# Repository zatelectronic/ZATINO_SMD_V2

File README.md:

<div align="center">

# ZATINO V2 SMD

**Placa de desenvolvimento compatível com Arduino Uno, totalmente SMD, com programação USB-C integrada via módulo FT232RL**

</div>

---

## 📋 Índice

- [ZATINO V2 SMD](#zatino-v2-smd)
  - [📋 Índice](#-índice)
  - [Visão Geral](#visão-geral)
  - [Renders 3D](#renders-3d)
  - [Funcionalidades](#funcionalidades)
  - [Especificações Técnicas](#especificações-técnicas)
  - [Lista de Materiais](#lista-de-materiais)
  - [Arquitetura de Alimentação](#arquitetura-de-alimentação)
  - [Compatibilidade de Pinos](#compatibilidade-de-pinos)
  - [Estrutura do Repositório](#estrutura-do-repositório)
  - [Como Usar](#como-usar)
    - [Abrindo no KiCad](#abrindo-no-kicad)
    - [Programando a Placa](#programando-a-placa)
  - [Sobre](#sobre)

---

## Visão Geral

**ZATINO V2 SMD** é uma placa de desenvolvimento personalizada, compatível com Arduino Uno, projetada do zero pela **ZAT ELECTRONIC** utilizando o **KICAD 10**. A placa substitui todos os componentes através-furo por componentes SMD, resultando em uma PCB mais limpa, compacta e com aparência profissional.

O projeto utiliza o **ATmega328PB-AU** (TQFP-32) como microcontrolador principal, com um módulo **FT232RL USB-C** encaixado em um conector fêmea de 6 pinos para programação serial e comunicação USB — mantendo o conector USB-C montado verticalmente na borda da placa para um acabamento elegante.

> 💡 Esta placa mantém **total compatibilidade de pinos com o Arduino Uno R3**, permitindo o uso de shields e bibliotecas existentes sem qualquer modificação.

---

## Renders 3D

<div align="center">

*Vista superior — posicionamento dos componentes e serigrafias*

<br/>

*Vista isométrica — módulo FT232RL USB-C e montagem geral da placa*

</div>

---

## Funcionalidades

- ✅ **ATmega328PB-AU** — encapsulamento SMD TQFP-32, 100% compatível com Arduino Uno
- ✅ **Programação via USB-C** pelo módulo FT232RL (conector plugável)
- ✅ **Duplo regulador de tensão** — 5V (AMS1117-5.0) e 3,3V (AMS1117-3.3)
- ✅ **Proteção contra inversão de polaridade** via diodo 1N4007 na entrada de alimentação
- ✅ **Oscilador a cristal de 16 MHz** (encapsulamento SMD HC-49/SD)
- ✅ **Pinout completo Arduino Uno R3** — conectores Digital, Analógico, Alimentação e ICSP
- ✅ **LEDs de status** (footprint SMD 1210)
- ✅ **Botão de reset tátil** (SMD 6×6×5 mm)
- ✅ **Entrada de alimentação Barrel Jack (P4)** com chave integrada
- ✅ **Projetado com KICAD 10** — EDA totalmente open source
- ✅ **Logotipo Open Source Hardware** certificado na PCB

---

## Especificações Técnicas

| Parâmetro | Valor |
|-----------|-------|
| **Microcontrolador** | ATmega328PB-AU (TQFP-32) |
| **Velocidade de Clock** | 16 MHz (cristal externo) |
| **Tensão de Operação** | 5V |
| **Tensão de Entrada** | 7–12V (Barrel Jack P4) |
| **Saída 3,3V** | AMS1117-3.3 (até 800mA) |
| **Regulador 5V** | AMS1117-5.0 |
| **Interface USB** | USB-C via módulo FT232RL |
| **Pinos Digital I/O** | 14 (D0–D13), PWM em D3, D5, D6, D9, D10, D11 |
| **Entradas Analógicas** | 6 (A0–A5) |
| **Memória Flash** | 32 KB (ATmega328PB) |
| **SRAM** | 2 KB |
| **EEPROM** | 1 KB |
| **Ferramenta de Projeto** | KICAD 10.0 |
| **Versão da PCB** | V2 — 2026 |
| **Fator de Forma** | Compatível com Arduino Uno R3 |

---

## Lista de Materiais

| Ref | Componente | Valor / Parte | Encapsulamento |
|-----|-----------|--------------|----------------|
| U2 | Microcontrolador | ATmega328PB-AU | TQFP-32 |
| REGULADOR_5V1 | Regulador de Tensão 5V | AMS1117-5.0 | SOT-223 |
| REGULADOR_3V3 | Regulador de Tensão 3,3V | AMS1117-3.3 | SOT-223 |
| KR1 | Oscilador a Cristal | 16 MHz | HC-49/SD SMD |
| BARRA_DE_PINO2 | Conector FTDI | FT232RL USB-C | Fêmea 6 pinos 2,54mm |
| A2 | Referência de Pinout | Arduino Uno R3 | — |
| D1 | Diodo Retificador | 1N4007 | SMA |
| L1, L2 | LEDs de Status | LED 5MM | 1210 (3225) SMD |
| R1 | Resistor de LED | 470Ω | 1206 |
| R2 | Resistor de LED | 220Ω | 1206 |
| R3 | Resistor de Pull-up | 10KΩ | 1206 |
| C1, C2, C3 | Capacitores Eletrolíticos | 10µF | CP Elec 4×5.4 |
| C4, C5 | Capacitores de Cristal | 22pF | 0805 |
| C6, C7 | Capacitores de Bypass | 100nF | 0805 |
| CONECTOR1 | Conector de Alimentação DC | Barrel Jack P4 | Horizontal |
| BARRA_DE_PINO1 | Conector Auxiliar | 2 terminais | 2,54mm |
| TACTIL_SWITCH1 | Botão de Reset | 6×6×5mm | SMD Tátil |
| TP1 | Ponto de Teste | — | SMD |

---

## Arquitetura de Alimentação

```
VIN (Barrel Jack P4)
        │
    [1N4007]  ← Proteção contra inversão de polaridade
        │
   ┌────┴────┐
   │         │
[AMS1117-5.0]  [AMS1117-3.3]
   │         │
  +5V       +3,3V
   │
[ATmega328PB-AU]
   │
[FT232RL USB-C] ← UART TX/RX + DTR (auto-reset)
```

A placa suporta duas fontes de alimentação:
- **Barrel Jack (P4)** — entrada de 7 a 12V DC, regulada para 5V e 3,3V internamente
- **USB-C via módulo FT232RL** — 5V direto do USB, alimentando o rail VCC quando conectado

---

## Compatibilidade de Pinos

A placa expõe o **pinout completo do Arduino Uno R3**:

| Conector | Pinos |
|----------|-------|
| Digital (PWM) | D0–D13, com PWM em ~3, ~5, ~6, ~9, ~10, ~11 |
| Entradas Analógicas | A0–A5 |
| Alimentação | VIN, 5V, 3V3, GND, AREF, IOREF, RESET |
| ICSP | MISO, MOSI, SCK, RESET, VCC, GND |
| UART (FT232RL) | TX, RX (via conector BARRA_DE_PINO2) |
| I2C | SDA (A4), SCL (A5) |

---

## Estrutura do Repositório

```
ZATINO_SMD_V2/
├── ZATINO_SMD_V2.kicad_pro       # Arquivo de projeto KiCad
├── ZATINO_SMD_V2.kicad_sch       # Esquemático (KICAD 10)
├── ZATINO_SMD_V2.kicad_pcb       # Layout da PCB (KICAD 10)
├── ZATINO_SMD_V2.kicad_prl       # Configurações locais do projeto
├── packages3D/                   # Modelos 3D arquivados (STEP / WRL)
│   ├── ATmega_AP214.STEP
│   ├── AMS1117_3V3_axisY.step
│   ├── AMS1117_5V_axisY.step
│   ├── Waveshare_FT232RL_USB-C.step
│   ├── Tactal Switch - SMD 6x6x5.stp
│   └── ...
├── fp-info-cache                 # Cache de footprints
├── fabrication-toolkit-options.json
├── imagem_1.png                  # Render superior da PCB
├── imagem_2.png                  # Render isométrico da PCB
└── README.md
```

---

## Como Usar

### Abrindo no KiCad

1. Instale o **KICAD 10.0** ou superior
2. Clone este repositório:
   ```bash
   git clone https://github.com/seu-usuario/ZATINO_SMD_V2.git
   ```
3. Abra o arquivo `ZATINO_SMD_V2.kicad_pro` no KiCad

### Programando a Placa

1. Encaixe o **módulo FT232RL USB-C** no conector de 6 pinos (`BARRA_DE_PINO2`)
2. Conecte via USB-C ao computador
3. Abra o **Arduino IDE** ou **PlatformIO**
4. Selecione a placa: **Arduino Uno**
5. Selecione a porta COM correta e faça o upload do sketch

## Sobre

<div align="center">

Projetado por **ZAT ELECTRONIC**

*ZATINO V2 SMD — 2026*

</div>

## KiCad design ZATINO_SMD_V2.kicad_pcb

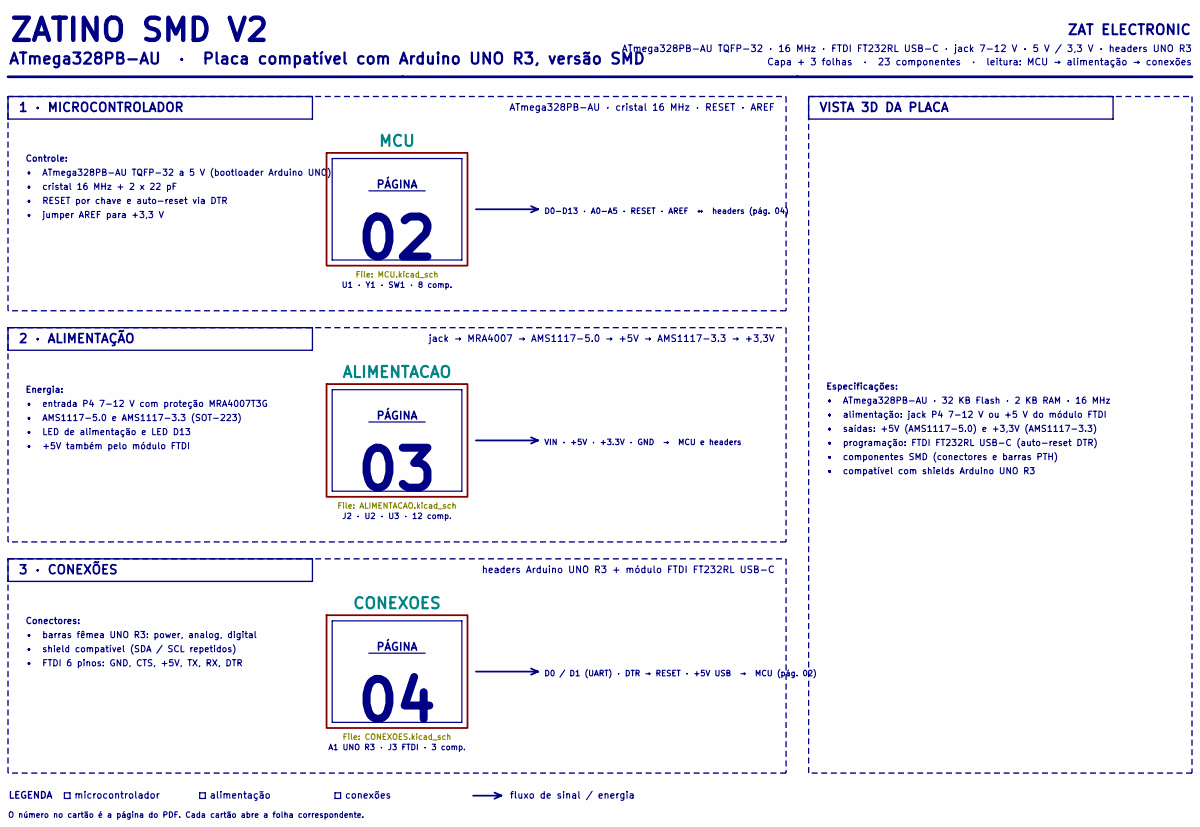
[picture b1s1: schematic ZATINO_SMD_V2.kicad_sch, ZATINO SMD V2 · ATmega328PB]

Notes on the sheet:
PÁGINA
VIN · +5V · +3.3V · GND → MCU e headers
conexões
• compatível com shields Arduino UNO R3
3 · CONEXÕES
• +5V também pelo módulo FTDI
U1 · Y1 · SW1 · 8 comp.
• componentes SMD (conectores e barras PTH)
• LED de alimentação e LED D13
Energia:
VISTA 3D DA PLACA
• ATmega328PB-AU TQFP-32 a 5 V (bootloader Arduino UNO)
• alimentação: jack P4 7-12 V ou +5 V do módulo FTDI
Capa + 3 folhas · 23 componentes · leitura: MCU → alimentação → conexões
D0-D13 · A0-A5 · RESET · AREF ↔ headers (pág. 04)
Especificações:
• RESET por chave e auto-reset via DTR
2 · ALIMENTAÇÃO
• shield compatível (SDA / SCL repetidos)
ZATINO SMD V2
O número no cartão é a página do PDF. Cada cartão abre a folha correspondente.
ATmega328PB-AU · cristal 16 MHz · RESET · AREF
ATmega328PB-AU · Placa compatível com Arduino UNO R3, versão SMD
• FTDI 6 pinos: GND, CTS, +5V, TX, RX, DTR
microcontrolador
• saídas: +5V (AMS1117-5.0) e +3,3V (AMS1117-3.3)
jack → MRA4007 → AMS1117-5.0 → +5V → AMS1117-3.3 → +3,3V
• barras fêmea UNO R3: power, analog, digital
ATmega328PB-AU TQFP-32 · 16 MHz · FTDI FT232RL USB-C · jack 7-12 V · 5 V / 3,3 V · headers UNO R3
A1 UNO R3 · J3 FTDI · 3 comp.
Conectores:
fluxo de sinal / energia
• cristal 16 MHz + 2 x 22 pF
J2 · U2 · U3 · 12 comp.
D0 / D1 (UART) · DTR → RESET · +5V USB → MCU (pág. 02)
• programação: FTDI FT232RL USB-C (auto-reset DTR)
LEGENDA
• ATmega328PB-AU · 32 KB Flash · 2 KB RAM · 16 MHz
• AMS1117-5.0 e AMS1117-3.3 (SOT-223)
• entrada P4 7-12 V com proteção MRA4007T3G

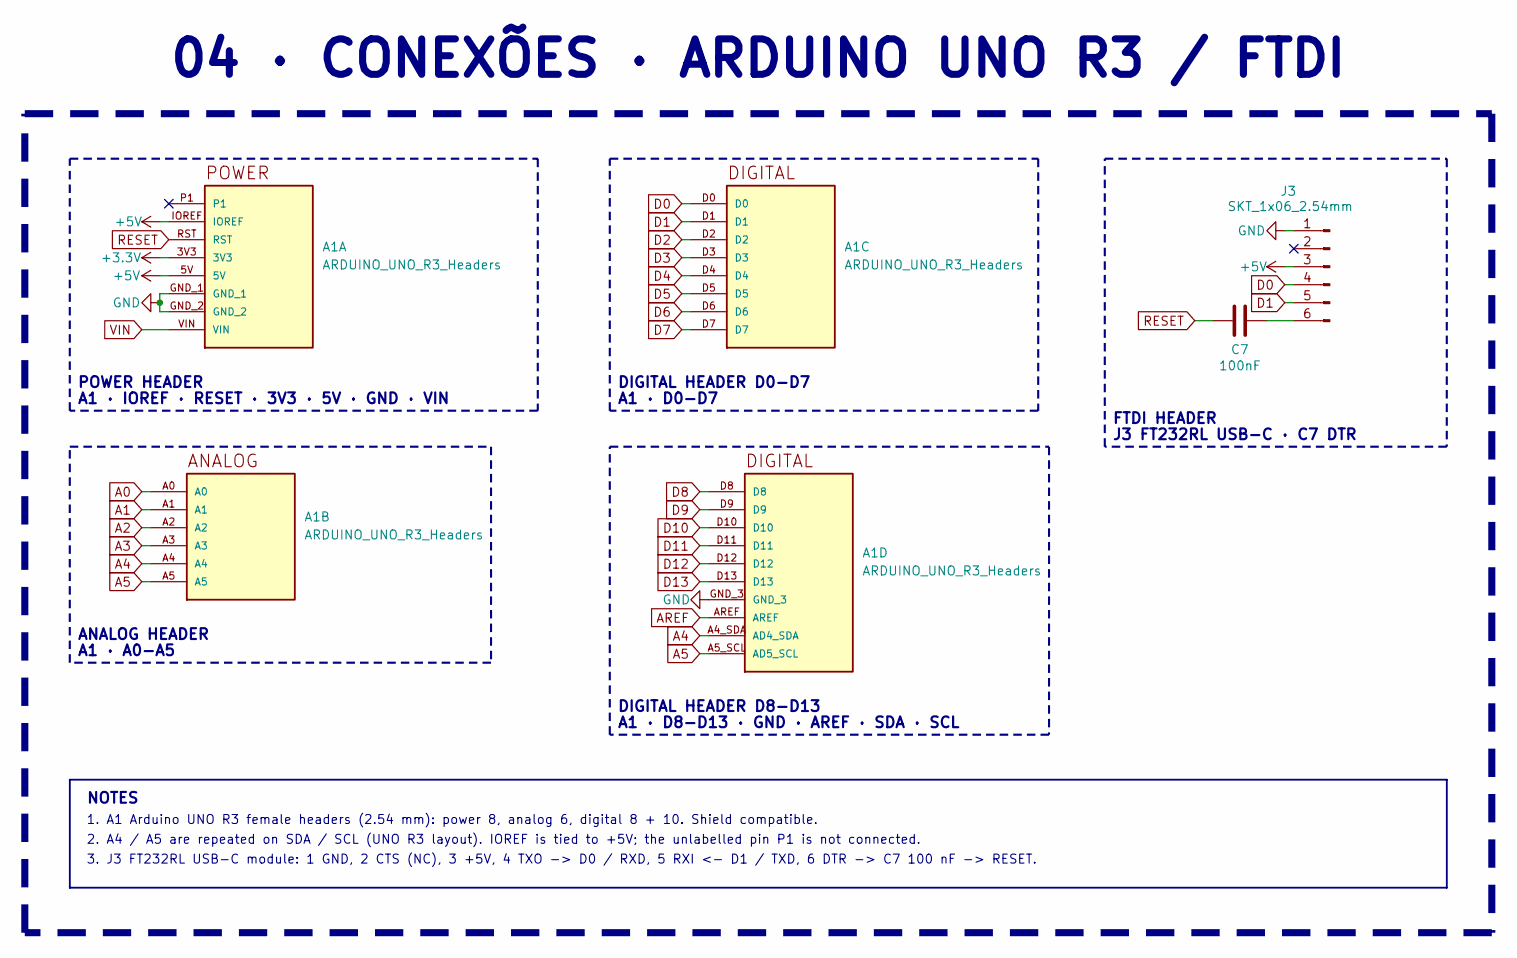
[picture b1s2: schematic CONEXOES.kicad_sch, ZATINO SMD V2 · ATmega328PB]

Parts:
A1: ARDUINO_UNO_R3_Headers
C7: 100nF; C_0805_2012Metric
J3: SKT_1x06_2.54mm; PinSocket_1x06_P2.54mm_Vertical_FT232RL_USB-C

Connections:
+3.3V: A1.3V3; also elsewhere on the board
+5V: A1.5V, A1.IOREF, J3.3; also elsewhere on the board
A0: A1.A0; also elsewhere on the board
A1: A1.A1; also elsewhere on the board
A2: A1.A2; also elsewhere on the board
A3: A1.A3; also elsewhere on the board
A4: A1.A4, A1.A4_SDA (AD4_SDA); also elsewhere on the board
A5: A1.A5, A1.A5_SCL (AD5_SCL); also elsewhere on the board
AREF: A1.AREF; also elsewhere on the board
D0: A1.D0, J3.4; also elsewhere on the board
D1: A1.D1, J3.5; also elsewhere on the board
D2: A1.D2; also elsewhere on the board
D3: A1.D3; also elsewhere on the board
D4: A1.D4; also elsewhere on the board
D5: A1.D5; also elsewhere on the board
D6: A1.D6; also elsewhere on the board
D7: A1.D7; also elsewhere on the board
D8: A1.D8; also elsewhere on the board
D9: A1.D9; also elsewhere on the board
D10: A1.D10; also elsewhere on the board
D11: A1.D11; also elsewhere on the board
D12: A1.D12; also elsewhere on the board
D13: A1.D13; also elsewhere on the board
GND: A1.GND_1, A1.GND_2, A1.GND_3, J3.1; also elsewhere on the board
unnamed: C7.1, J3.6
RESET: A1.RST, C7.2; also elsewhere on the board
VIN: A1.VIN; also elsewhere on the board

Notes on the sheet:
FTDI HEADER
DIGITAL HEADER D0-D7
A1 · D0-D7
1. A1 Arduino UNO R3 female headers (2.54 mm): power 8, analog 6, digital 8 + 10. Shield compatible.
J3 FT232RL USB-C · C7 DTR
ANALOG HEADER
04 · CONEXÕES · ARDUINO UNO R3 / FTDI
2. A4 / A5 are repeated on SDA / SCL (UNO R3 layout). IOREF is tied to +5V; the unlabelled pin P1 is not connected.
DIGITAL HEADER D8-D13
A1 · D8-D13 · GND · AREF · SDA · SCL
3. J3 FT232RL USB-C module: 1 GND, 2 CTS (NC), 3 +5V, 4 TXO -> D0 / RXD, 5 RXI <- D1 / TXD, 6 DTR -> C7 100 nF -> RESET.
A1 · A0-A5
POWER HEADER
A1 · IOREF · RESET · 3V3 · 5V · GND · VIN
NOTES

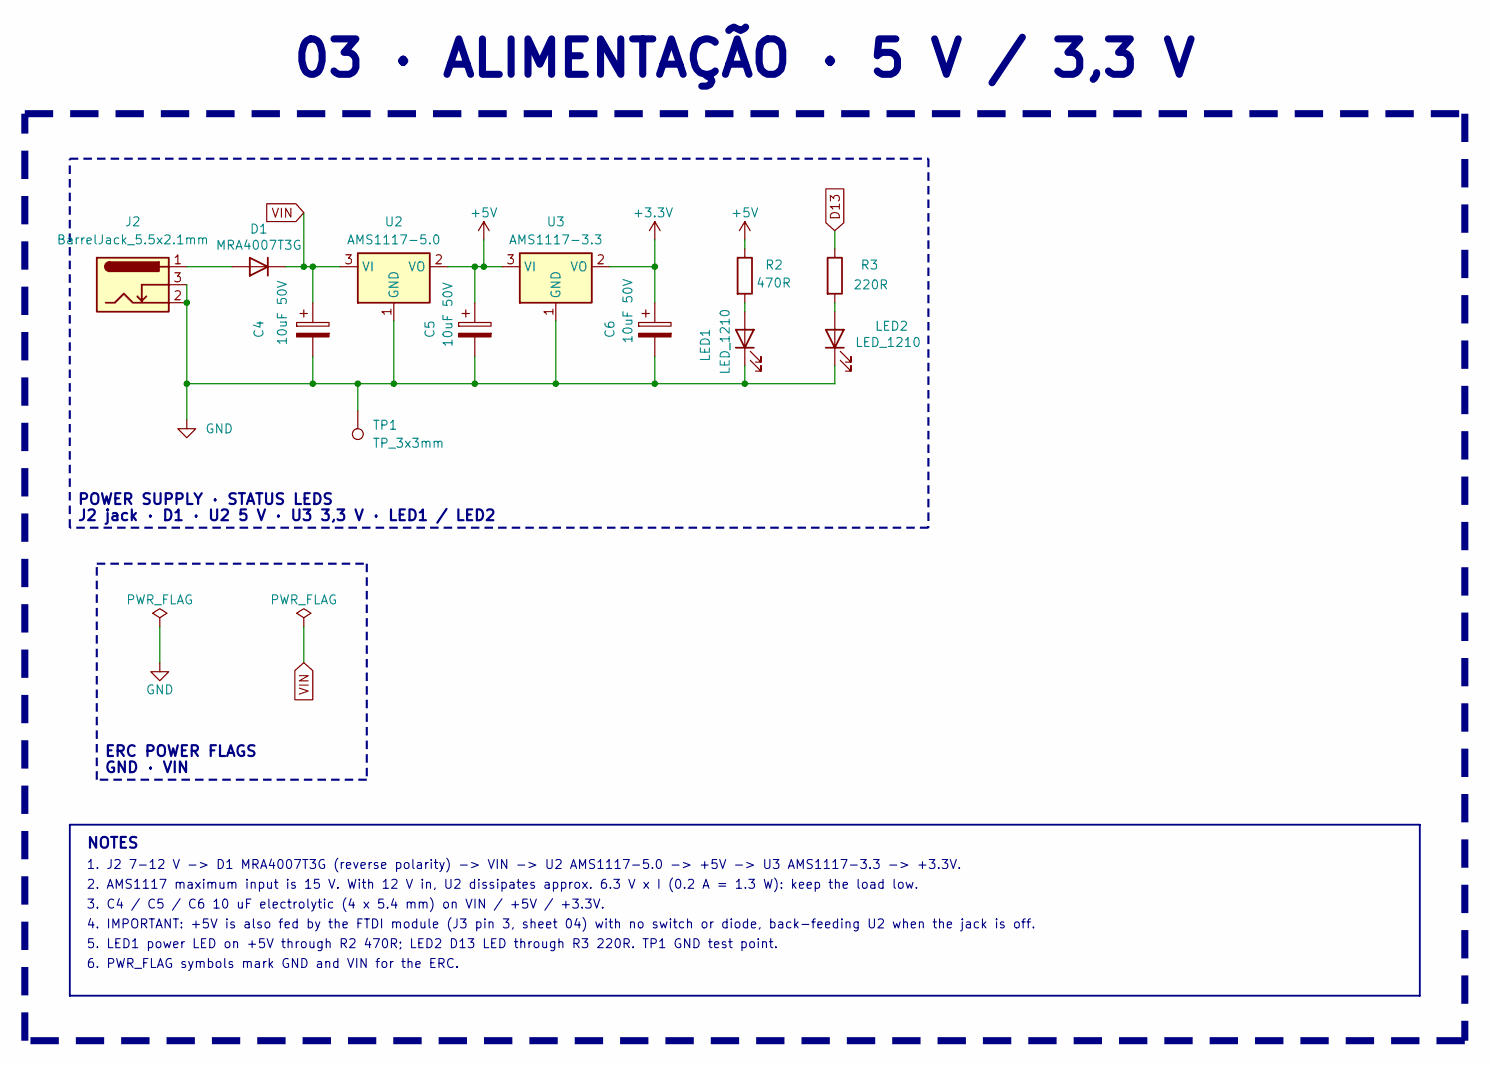
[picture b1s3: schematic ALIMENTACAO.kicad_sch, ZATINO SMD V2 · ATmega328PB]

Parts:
C4, C5, C6: 10uF 50V; CP_Elec_4x5.4
D1: MRA4007T3G; D_SMA
J2: BarrelJack_5.5x2.1mm; BarrelJack_Horizontal_EdgeMount
LED1, LED2: LED_1210; LED_1210_3225Metric
R2: 470R; R_1206_3216Metric
R3: 220R; R_1206_3216Metric
TP1: TP_3x3mm; TestPoint_Pad_3.0x3.0mm
U2: AMS1117-5.0; SOT-223-3_TabPin2_AMS1117-5.0
U3: AMS1117-3.3; SOT-223-3_TabPin2_AMS1117-3.3

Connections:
+3.3V: C6.1, U3.2 (VO); also elsewhere on the board
+5V: C5.1, R2.1, U2.2 (VO), U3.3 (VI); also elsewhere on the board
D13: R3.1; also elsewhere on the board
GND: C4.2, C5.2, C6.2, J2.2, J2.3, LED1.1 (K), LED2.1 (K), TP1.1 (1_1), U2.1 (GND), U3.1 (GND); also elsewhere on the board
unnamed: D1.2 (A), J2.1
unnamed: LED1.2 (A), R2.2
unnamed: LED2.2 (A), R3.2
VIN: C4.1, D1.1 (K), U2.3 (VI); also elsewhere on the board

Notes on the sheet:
2. AMS1117 maximum input is 15 V. With 12 V in, U2 dissipates approx. 6.3 V x I (0.2 A = 1.3 W): keep the load low.
NOTES
5. LED1 power LED on +5V through R2 470R; LED2 D13 LED through R3 220R. TP1 GND test point.
6. PWR_FLAG symbols mark GND and VIN for the ERC.
4. IMPORTANT: +5V is also fed by the FTDI module (J3 pin 3, sheet 04) with no switch or diode, back-feeding U2 when the jack is off.
3. C4 / C5 / C6 10 uF electrolytic (4 x 5.4 mm) on VIN / +5V / +3.3V.
ERC POWER FLAGS
GND · VIN
J2 jack · D1 · U2 5 V · U3 3,3 V · LED1 / LED2
POWER SUPPLY · STATUS LEDS
03 · ALIMENTAÇÃO · 5 V / 3,3 V
1. J2 7-12 V -> D1 MRA4007T3G (reverse polarity) -> VIN -> U2 AMS1117-5.0 -> +5V -> U3 AMS1117-3.3 -> +3.3V.

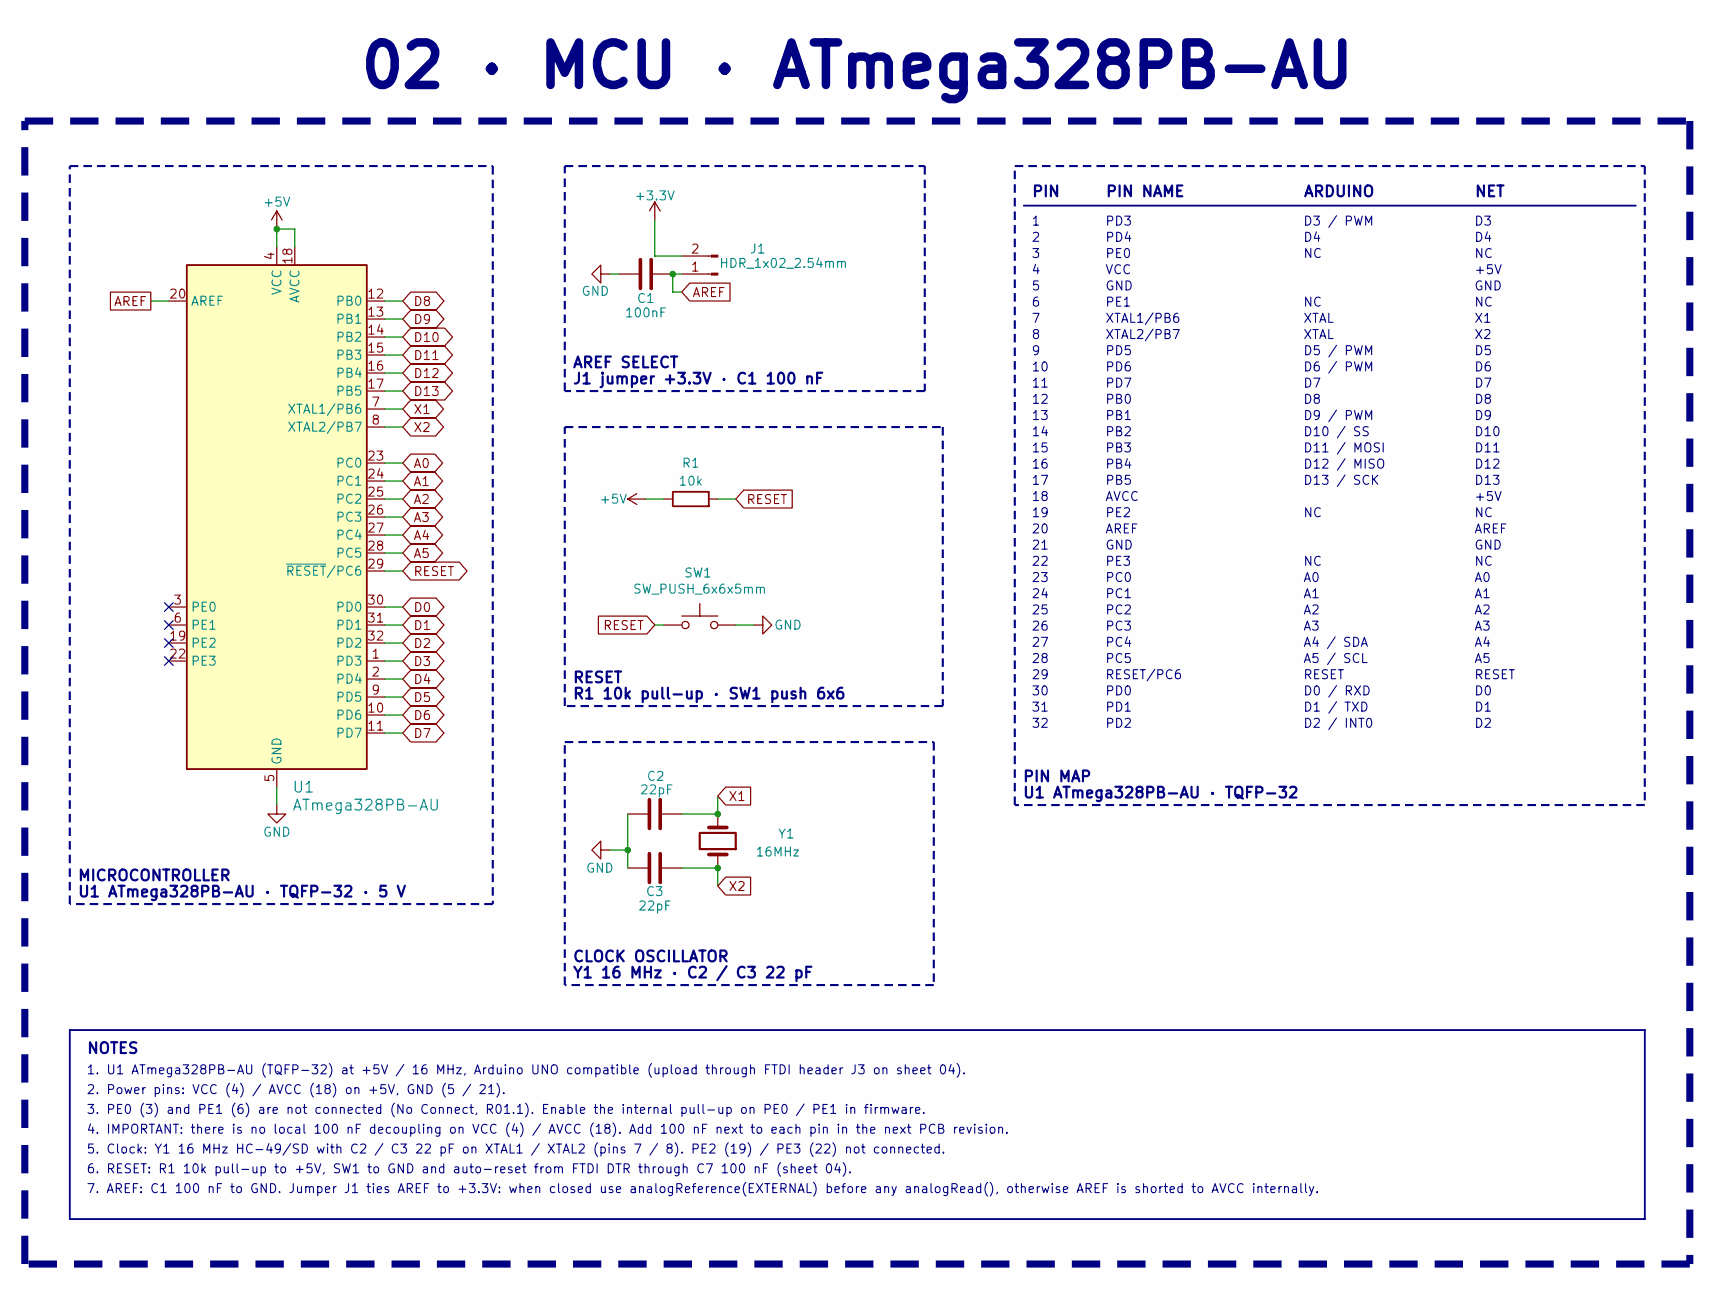
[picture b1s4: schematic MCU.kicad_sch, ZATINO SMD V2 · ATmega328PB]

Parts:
C1: 100nF; C_0805_2012Metric
C2, C3: 22pF; C_0805_2012Metric
J1: HDR_1x02_2.54mm; PinHeader_1x02_P2.54mm_Vertical
R1: 10k; R_1206_3216Metric
SW1: SW_PUSH_6x6x5mm; SW_SPST_PTS645Sx43SMTR92_6x6x5mm
U1: ATmega328PB-AU; TQFP-32_7x7mm_P0.8mm_ATmega328PB-AU
Y1: 16MHz; Crystal_SMD_HC49-SD

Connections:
+3.3V: J1.2; also elsewhere on the board
+5V: R1.1, U1.4 (VCC), U1.18 (AVCC); also elsewhere on the board
A0: U1.23 (PC0); also elsewhere on the board
A1: U1.24 (PC1); also elsewhere on the board
A2: U1.25 (PC2); also elsewhere on the board
A3: U1.26 (PC3); also elsewhere on the board
A4: U1.27 (PC4); also elsewhere on the board
A5: U1.28 (PC5); also elsewhere on the board
AREF: C1.2, J1.1, U1.20 (AREF); also elsewhere on the board
D0: U1.30 (PD0); also elsewhere on the board
D1: U1.31 (PD1); also elsewhere on the board
D2: U1.32 (PD2); also elsewhere on the board
D3: U1.1 (PD3); also elsewhere on the board
D4: U1.2 (PD4); also elsewhere on the board
D5: U1.9 (PD5); also elsewhere on the board
D6: U1.10 (PD6); also elsewhere on the board
D7: U1.11 (PD7); also elsewhere on the board
D8: U1.12 (PB0); also elsewhere on the board
D9: U1.13 (PB1); also elsewhere on the board
D10: U1.14 (PB2); also elsewhere on the board
D11: U1.15 (PB3); also elsewhere on the board
D12: U1.16 (PB4); also elsewhere on the board
D13: U1.17 (PB5); also elsewhere on the board
GND: C1.1, C2.2, C3.2, SW1.2, U1.5 (GND), U1.21 (GND); also elsewhere on the board
RESET: R1.2, SW1.1, U1.29 (~RESET/PC6); also elsewhere on the board
X1: C2.1, U1.7 (XTAL1/PB6), Y1.2
X2: C3.1, U1.8 (XTAL2/PB7), Y1.1

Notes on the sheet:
PD2
XTAL
XTAL1/PB6
ARDUINO
PE2
PD5
AVCC
D10 / SS
D5 / PWM
D11
PD4
RESET
NOTES
PD7
NET
1. U1 ATmega328PB-AU (TQFP-32) at +5V / 16 MHz, Arduino UNO compatible (upload through FTDI header J3 on sheet 04).
3. PE0 (3) and PE1 (6) are not connected (No Connect, R01.1). Enable the internal pull-up on PE0 / PE1 in firmware.
D9 / PWM
GND
PD1
PE0
D11 / MOSI
D13 / SCK
5. Clock: Y1 16 MHz HC-49/SD with C2 / C3 22 pF on XTAL1 / XTAL2 (pins 7 / 8). PE2 (19) / PE3 (22) not connected.
02 · MCU · ATmega328PB-AU
A5 / SCL
2. Power pins: VCC (4) / AVCC (18) on +5V, GND (5 / 21).
D13
PB1
D1 / TXD
D12
Y1 16 MHz · C2 / C3 22 pF
D2 / INT0
PB4
AREF SELECT
PB2
D12 / MISO
D10
AREF
PC4

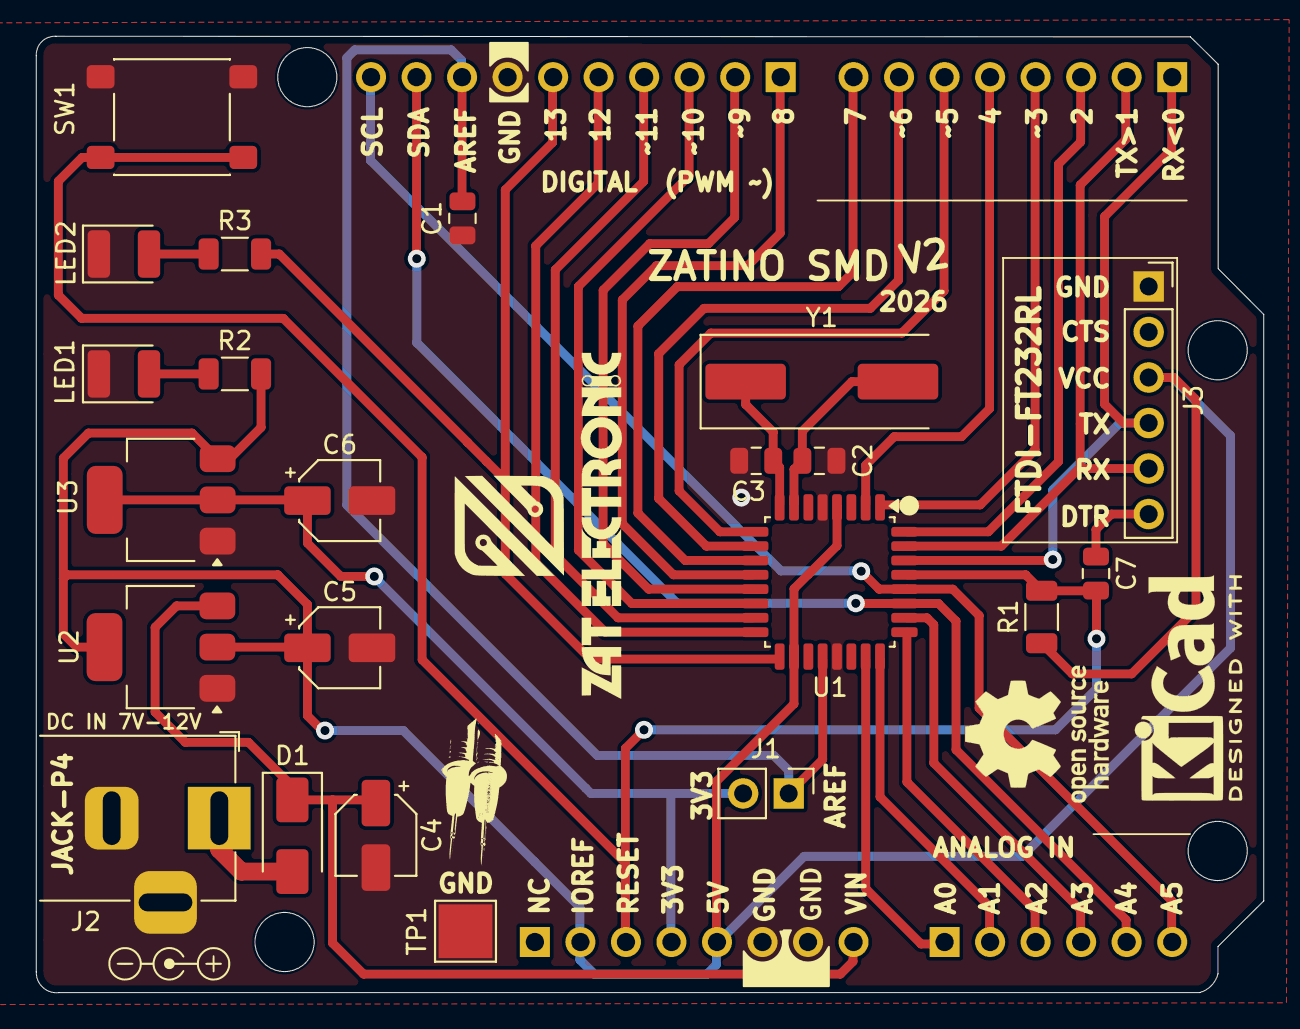
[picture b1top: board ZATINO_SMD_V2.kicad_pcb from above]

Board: 2 copper layers, 68.5 x 53.4 mm, 23 parts (0 on the bottom side), 32 nets.

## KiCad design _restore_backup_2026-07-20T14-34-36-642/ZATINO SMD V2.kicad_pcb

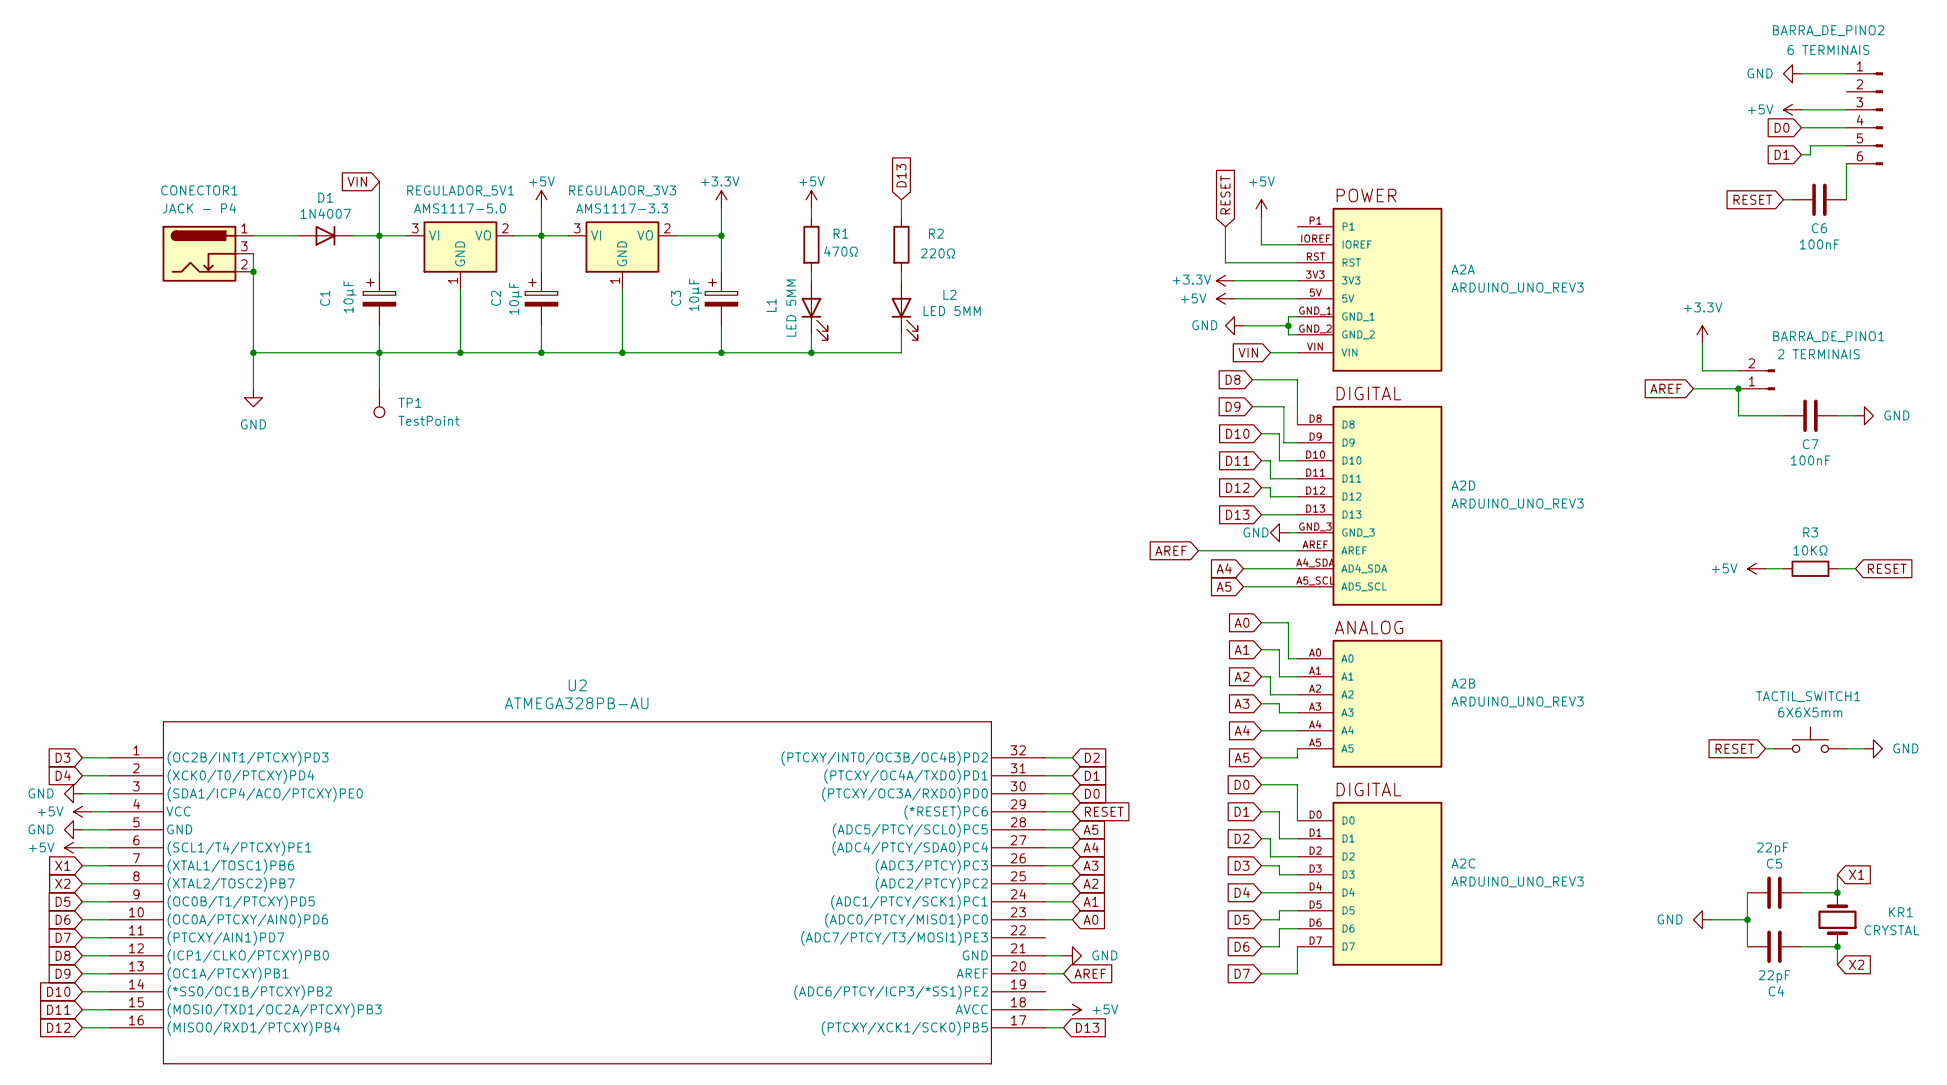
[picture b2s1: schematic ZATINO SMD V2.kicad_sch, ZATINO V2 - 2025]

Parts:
A2: ARDUINO_UNO_REV3; ARDUINO_ARDUINO_UNO_REV3; PARTREV N/A
BARRA_DE_PINO1: 2 TERMINAIS; PinHeader_1x02_P2.54mm_Vertical
BARRA_DE_PINO2: 6 TERMINAIS; PinHeader_1x06_P2.54mm_Vertical
C1, C2, C3: 10μF; CP_Elec_4x5.4
C4, C5: 22pF; C_0805_2012Metric
C6, C7: 100nF; C_0805_2012Metric
CONECTOR1: JACK - P4; BarrelJack_Horizontal
D1: 1N4007; D_SMA
KR1: CRYSTAL; Crystal_SMD_HC49-SD
L1, L2: LED 5MM; LED_1210_3225Metric
R1: 470Ω; R_1206_3216Metric
R2: 220Ω; R_1206_3216Metric
R3: 10KΩ; R_1206_3216Metric
REGULADOR_3V3: AMS1117-3.3; SOT-223-3_TabPin2
REGULADOR_5V1: AMS1117-5.0; SOT-223-3_TabPin2
TACTIL_SWITCH1: 6X6X5mm; SW_Push_1P1T_NO_6x6mm_H9.5mm
TP1: TestPoint; TestPoint_Pad_3.0x3.0mm
U2: ATMEGA328PB-AU; ATMEGA328PB_AU_MCH-M

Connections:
+3.3V: A2.3V3, BARRA_DE_PINO1.2, C3.1, REGULADOR_3V3.2 (VO)
+5V: A2.5V, A2.IOREF, BARRA_DE_PINO2.3, C2.1, R1.1, R3.1, REGULADOR_3V3.3 (VI), REGULADOR_5V1.2 (VO), U2.4 (VCC), U2.6 ((SCL1/T4/PTCXY)PE1), U2.18 (AVCC)
A0: A2.A0, U2.23 ((ADC0/PTCY/MISO1)PC0)
A1: A2.A1, U2.24 ((ADC1/PTCY/SCK1)PC1)
A2: A2.A2, U2.25 ((ADC2/PTCY)PC2)
A3: A2.A3, U2.26 ((ADC3/PTCY)PC3)
A4: A2.A4, A2.A4_SDA (AD4_SDA), U2.27 ((ADC4/PTCY/SDA0)PC4)
A5: A2.A5, A2.A5_SCL (AD5_SCL), U2.28 ((ADC5/PTCY/SCL0)PC5)
AREF: A2.AREF, BARRA_DE_PINO1.1, C7.2, U2.20 (AREF)
D0: A2.D0, BARRA_DE_PINO2.4, U2.30 ((PTCXY/OC3A/RXD0)PD0)
D1: A2.D1, BARRA_DE_PINO2.5, U2.31 ((PTCXY/OC4A/TXD0)PD1)
D2: A2.D2, U2.32 ((PTCXY/INT0/OC3B/OC4B)PD2)
D3: A2.D3, U2.1 ((OC2B/INT1/PTCXY)PD3)
D4: A2.D4, U2.2 ((XCK0/T0/PTCXY)PD4)
D5: A2.D5, U2.9 ((OC0B/T1/PTCXY)PD5)
D6: A2.D6, U2.10 ((OC0A/PTCXY/AIN0)PD6)
D7: A2.D7, U2.11 ((PTCXY/AIN1)PD7)
D8: A2.D8, U2.12 ((ICP1/CLKO/PTCXY)PB0)
D9: A2.D9, U2.13 ((OC1A/PTCXY)PB1)
D10: A2.D10, U2.14 ((*SS0/OC1B/PTCXY)PB2)
D11: A2.D11, U2.15 ((MOSI0/TXD1/OC2A/PTCXY)PB3)
D12: A2.D12, U2.16 ((MISO0/RXD1/PTCXY)PB4)
D13: A2.D13, R2.1, U2.17 ((PTCXY/XCK1/SCK0)PB5)
GND: A2.GND_1, A2.GND_2, A2.GND_3, BARRA_DE_PINO2.1, C1.2, C2.2, C3.2, C4.2, C5.2, C7.1, CONECTOR1.2, CONECTOR1.3, L1.1 (K), L2.1 (K), REGULADOR_3V3.1 (GND), REGULADOR_5V1.1 (GND), TACTIL_SWITCH1.2, TP1.1, U2.3 ((SDA1/ICP4/ACO/PTCXY)PE0), U2.5 (GND), U2.21 (GND)
unnamed: BARRA_DE_PINO2.6, C6.1
unnamed: CONECTOR1.1, D1.2 (A)
unnamed: L1.2 (A), R1.2
unnamed: L2.2 (A), R2.2
RESET: A2.RST, C6.2, R3.2, TACTIL_SWITCH1.1, U2.29 ((*RESET)PC6)
VIN: A2.VIN, C1.1, D1.1 (K), REGULADOR_5V1.3 (VI)
X1: C5.1, KR1.2, U2.7 ((XTAL1/TOSC1)PB6)
X2: C4.1, KR1.1, U2.8 ((XTAL2/TOSC2)PB7)

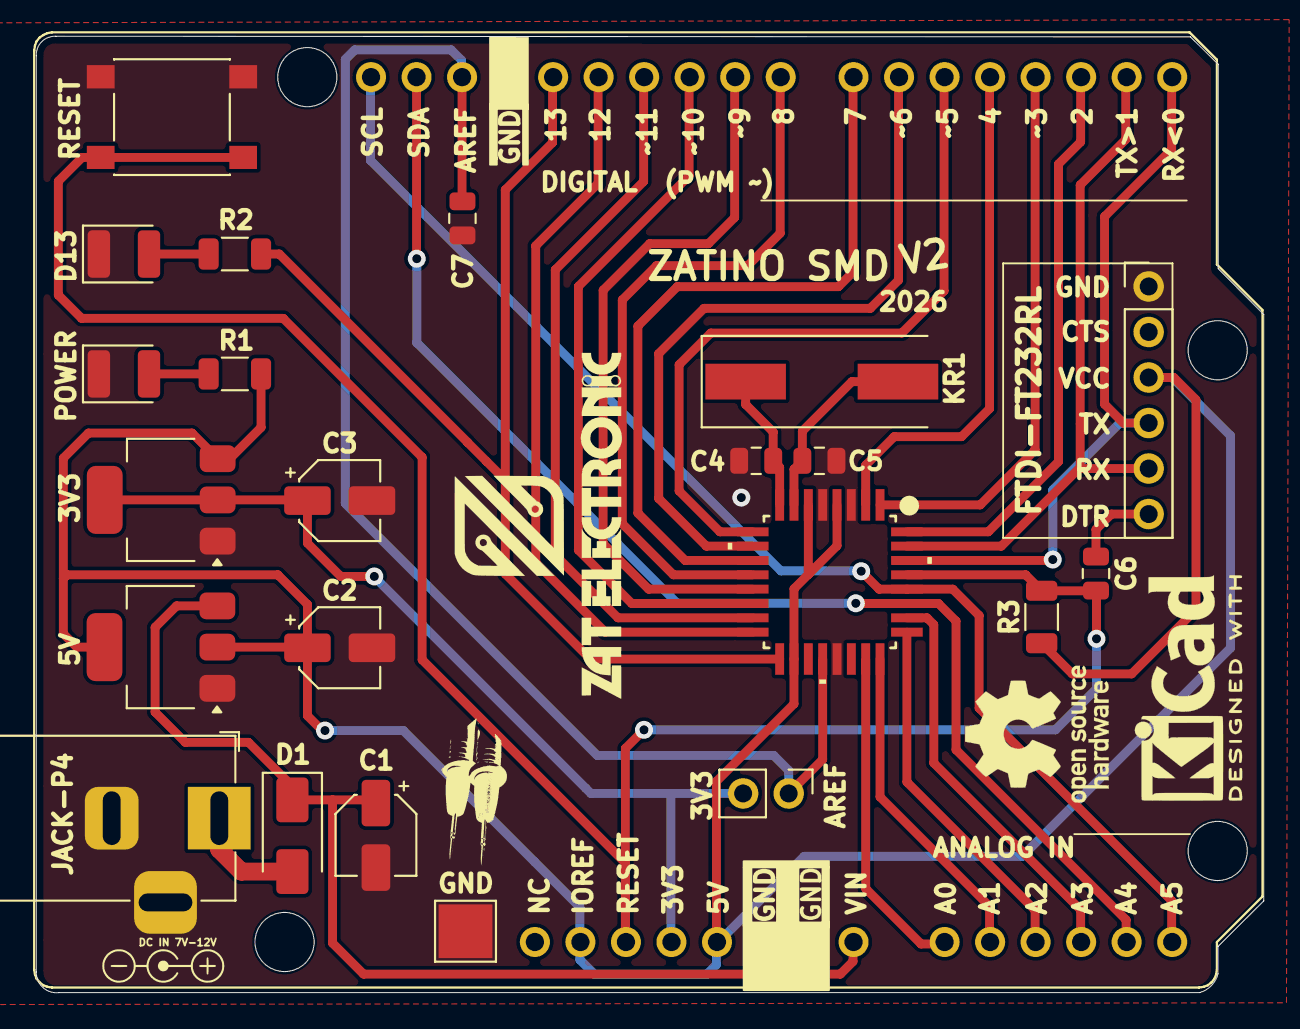
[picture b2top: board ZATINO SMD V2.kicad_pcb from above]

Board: 2 copper layers, 68.5 x 53.4 mm, 23 parts (0 on the bottom side), 32 nets.

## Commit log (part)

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2026-06-03 COMMIT-02-06-2026
2026-06-28 commint-1
2026-06-28 commit_3
2026-06-28 commit-4
2026-06-29 COMMIT-5
2026-06-29 COMMIT-6
